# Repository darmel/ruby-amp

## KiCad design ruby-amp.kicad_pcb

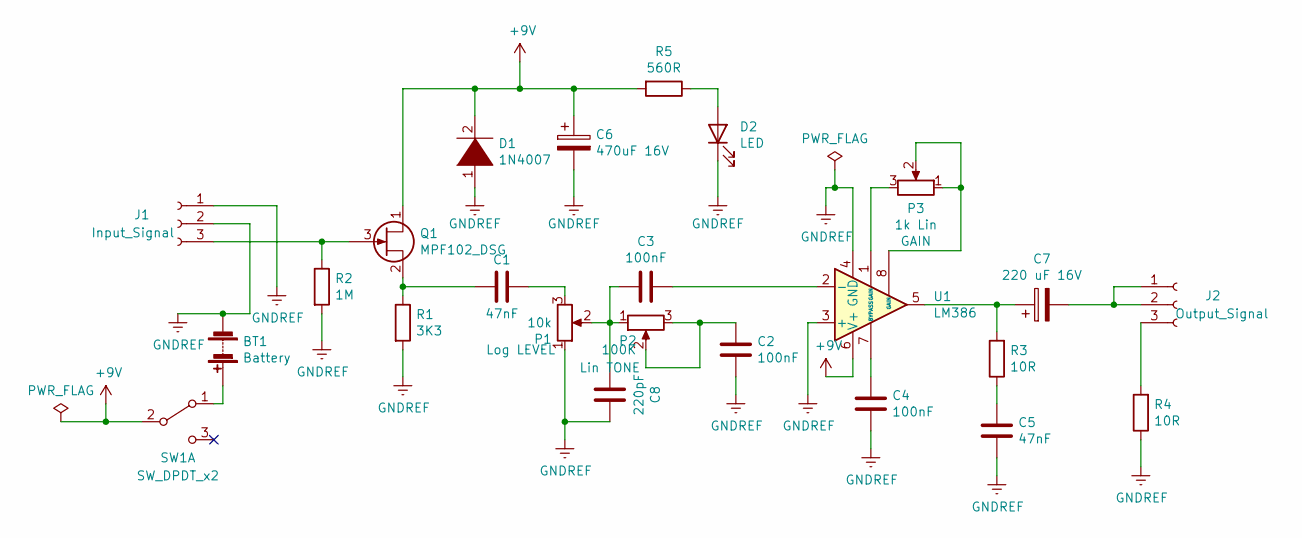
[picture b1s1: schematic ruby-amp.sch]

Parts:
BT1: Battery; PinHeader_1x02_P2.54mm_Vertical
C1: 47nF; C_Disc_D5.1mm_W3.2mm_P5.00mm
C2, C3, C4: 100nF; C_Disc_D4.3mm_W1.9mm_P5.00mm
C5: 47nF; C_Disc_D4.3mm_W1.9mm_P5.00mm
C6: 470uF 16V; CP_Radial_D8.0mm_P5.00mm
C7: 220 uF 16V; CP_Radial_D8.0mm_P5.00mm
C8: 220pF; C_Disc_D4.3mm_W1.9mm_P5.00mm
D1: 1N4007; D_A-405_P12.70mm_Horizontal
D2: LED; LED_D5.0mm_Clear
J1: Input_Signal; PinHeader_1x03_P2.54mm_Horizontal
J2: Output_Signal; PinHeader_1x03_P2.54mm_Horizontal
P1: 10k; PinHeader_1x03_P2.54mm_Horizontal
P2: 100K; PinHeader_1x03_P2.54mm_Horizontal
P3: 1k Lin; PinHeader_1x03_P2.54mm_Horizontal
Q1: MPF102_DSG; TO-92_Inline
R1: 3K3; R_Axial_DIN0207_L6.3mm_D2.5mm_P10.16mm_Horizontal
R2: 1M; R_Axial_DIN0207_L6.3mm_D2.5mm_P10.16mm_Horizontal
R3, R4: 10R; R_Axial_DIN0207_L6.3mm_D2.5mm_P10.16mm_Horizontal
R5: 560R; R_Axial_DIN0207_L6.3mm_D2.5mm_P10.16mm_Horizontal
SW1: SW_DPDT_x2; SW_CuK_JS202011CQN_DPDT_Straight
U1: LM386; DIP-8_W7.62mm_Socket

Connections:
+9V: C6.1, D1.2 (A), Q1.1 (D), R5.2, SW1.2 (B), U1.6 (V+)
GNDREF: BT1.2 (-), C2.1, C4.1, C5.1, C6.2, C8.1, D1.1 (K), D2.1 (K), J1.1, J1.2, P1.1, R1.2, R2.2, R4.1, U1.3 (+), U1.4 (GND)
unnamed: BT1.1 (+), SW1.1 (A)
unnamed: C1.1, P1.3
unnamed: C1.2, Q1.2 (S), R1.1
unnamed: C2.2, P2.2, P2.3
unnamed: C3.1, U1.2 (-)
unnamed: C3.2, C8.2, P1.2, P2.1
unnamed: C4.2, U1.7 (BYPASS)
unnamed: C5.2, R3.1
unnamed: C7.1, R3.2, U1.5
unnamed: C7.2, J2.1, J2.2
unnamed: D2.2 (A), R5.1
unnamed: J1.3, Q1.3 (G), R2.1
unnamed: J2.3, R4.2
unnamed: P3.1, P3.2, U1.8 (GAIN)
unnamed: P3.3, U1.1 (GAIN)

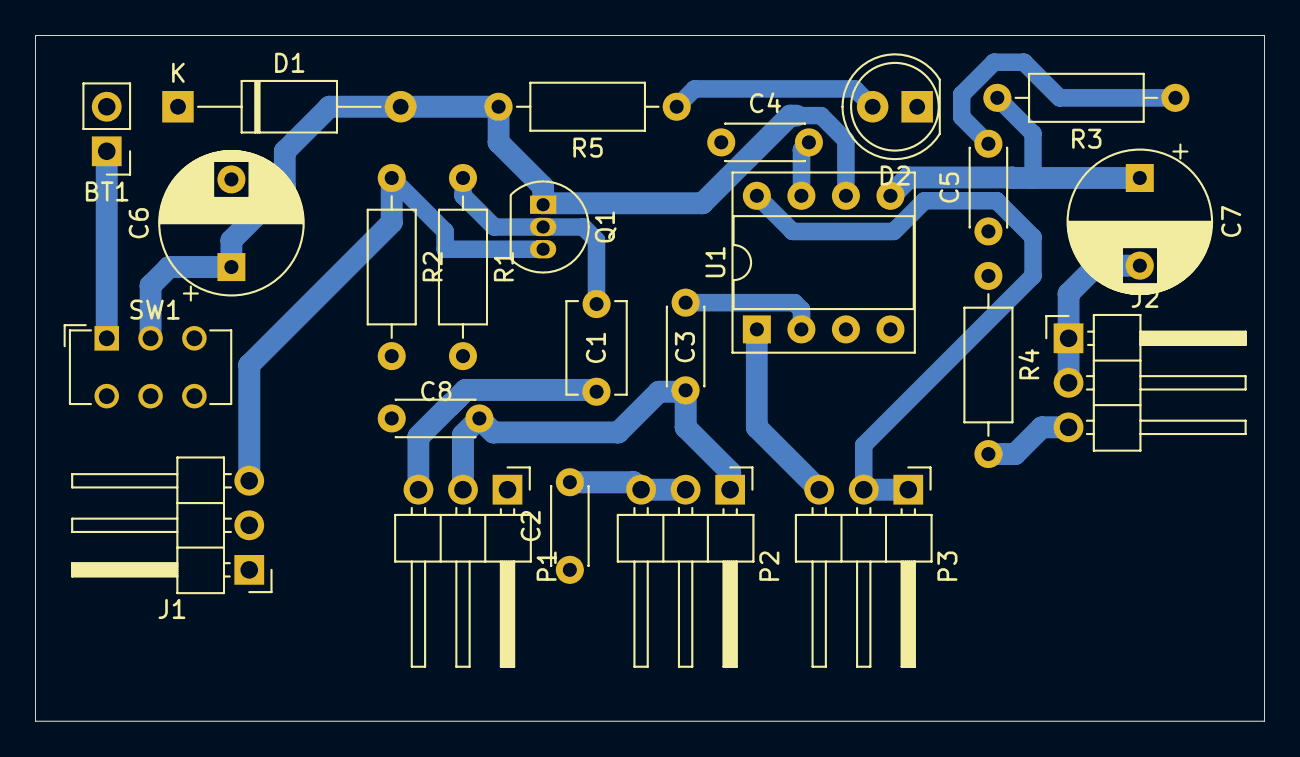
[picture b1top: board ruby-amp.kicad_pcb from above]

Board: 2 copper layers, 70.1 x 39.1 mm, 24 parts (0 on the bottom side), 17 nets.

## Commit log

2021-06-06 esquematico original listo
2021-06-06 footprint listo, netlist listo, PCB empezado
2021-06-10 PCB primera iteración
